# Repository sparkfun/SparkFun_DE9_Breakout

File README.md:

SparkFun DE9 Breakouts (Male and Female)
========================================
<table class="table table-hover table-striped table-bordered">
  <tr align="center">
   <td></td> 
   <td></td>
  </tr>
  <tr align="center">
    <td><a href="https://www.sparkfun.com/sparkfun-de9-breakout-male.html">SparkFun DE9 Breakout - Male <br />(BOB-29195)</a></td>
    <td><a href="https://www.sparkfun.com/sparkfun-de9-breakout-female.html">SparkFun DE9 Breakout - Female <br />(BOB-29196)</a></td>
  </tr>
</table>

The SparkFun DE9 Breakout - Male and DE9 Breakout - Female are simple breakout boards for a DE9 (commonly referred to as DB9) type connectors. These breakouts route all 9 pins from the connector, along with a pair of ground pins, to a 0.1"-spaced plated through-hole header. The boards also have two mounting holes that fit a 4-40 screw.

Repository Contents
-------------------
* **/Hardware** - Eagle design files (.brd, .sch)

Product Versions
----------------
* [BOB-29195](https://www.sparkfun.com/sparkfun-de9-breakout-male.html) - SparkFun DE9 Breakout - Male Initial Release
* [BOB-29196](https://www.sparkfun.com/sparkfun-de9-breakout-female.html) - SparkFun DE9 Breakout - Female Initial Release

License Information
-------------------

This product is _**open source**_! 

Please review the LICENSE.md file for license information. 

If you have any questions or concerns on licensing, please contact technical support on our [SparkFun forums](https://forum.sparkfun.com/viewforum.php?f=152).

Distributed as-is; no warranty is given.

- Your friends at SparkFun.

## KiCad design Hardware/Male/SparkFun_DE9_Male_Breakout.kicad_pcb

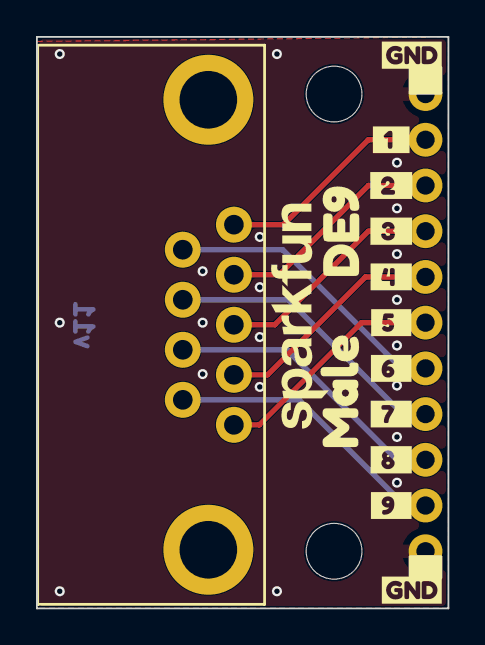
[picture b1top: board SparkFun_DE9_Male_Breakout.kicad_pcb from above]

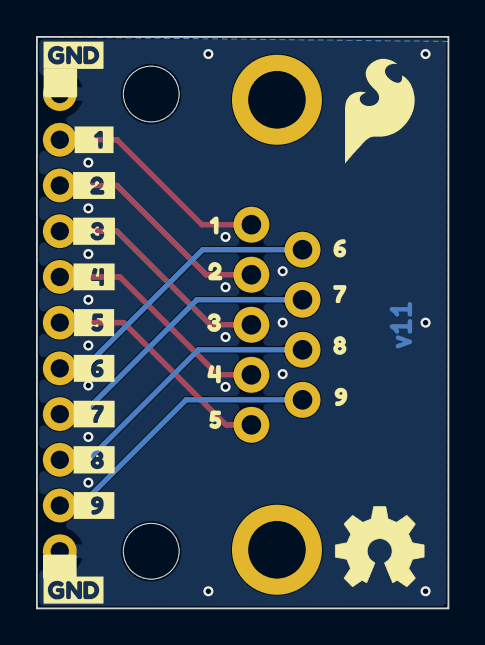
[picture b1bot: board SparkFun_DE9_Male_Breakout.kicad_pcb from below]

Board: 2 copper layers, 22.9 x 31.8 mm, 41 parts (22 on the bottom side), 10 nets.

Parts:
G3: OSHW_Logo; Creative_Commons_License
J1, J4: Conn_01x01; 1x01
J2: Conn_01x09; 1x09
J3: DE9 Header; DE9_Header_Horizontal_PTH
Ref**: Val**; OSHW_Logo_5mm
ST1, ST2: Stand_off; Standoff
kibuzzard-67D496B8: G***; kibuzzard-67D496B8
kibuzzard-67D496C7: G***; kibuzzard-67D496C7
kibuzzard-67D496CD: G***; kibuzzard-67D496CD
kibuzzard-67D496D5: G***; kibuzzard-67D496D5
kibuzzard-67D496DD: G***; kibuzzard-67D496DD
kibuzzard-67D496E4: G***; kibuzzard-67D496E4
kibuzzard-67D496EA: G***; kibuzzard-67D496EA
kibuzzard-67D496F6: G***; kibuzzard-67D496F6
kibuzzard-67D49687: G***; kibuzzard-67D49687
kibuzzard-67D49838: G***; kibuzzard-67D49838
kibuzzard-67DB37C8: G***; kibuzzard-67DB37C8
kibuzzard-67DDA3A2: G***; kibuzzard-67DDA3A2
kibuzzard-67DDA3AA: G***; kibuzzard-67DDA3AA
kibuzzard-67DDA3B0: G***; kibuzzard-67DDA3B0
kibuzzard-67DDA3B8: G***; kibuzzard-67DDA3B8
kibuzzard-67DDA3D5: G***; kibuzzard-67DDA3D5
kibuzzard-67DDA3E0: G***; kibuzzard-67DDA3E0
kibuzzard-67DDA391: G***; kibuzzard-67DDA391
kibuzzard-67DDA399: G***; kibuzzard-67DDA399
kibuzzard-67DDBC91, kibuzzard-67DDBC91#2, kibuzzard-67DDBC91#3, kibuzzard-67DDBC91#4: G***; kibuzzard-67DDBC91
kibuzzard-67DDBDB0: G***; kibuzzard-67DDBDB0
kibuzzard-67DDBDCA: G***; kibuzzard-67DDBDCA
kibuzzard-67DDBDCE: G***; kibuzzard-67DDBDCE
kibuzzard-67DDBDD2: G***; kibuzzard-67DDBDD2
kibuzzard-67DDBDD7: G***; kibuzzard-67DDBDD7
kibuzzard-67DDBDDC: G***; kibuzzard-67DDBDDC
kibuzzard-67DDBDF0: G***; kibuzzard-67DDBDF0
kibuzzard-67DDBDF6: G***; kibuzzard-67DDBDF6
kibuzzard-67DDBDFC: G***; kibuzzard-67DDBDFC
kibuzzard-67F7FDBF: G***; kibuzzard-67F7FDBF

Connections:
GND: J1.1 (Pin_1_1), J4.1 (Pin_1_1)
unnamed: J2.1, J3.1
unnamed: J2.2, J3.2
unnamed: J2.3, J3.3
unnamed: J2.4, J3.4
unnamed: J2.5, J3.5
unnamed: J2.6, J3.6
unnamed: J2.7, J3.7
unnamed: J2.8, J3.8
unnamed: J2.9, J3.9

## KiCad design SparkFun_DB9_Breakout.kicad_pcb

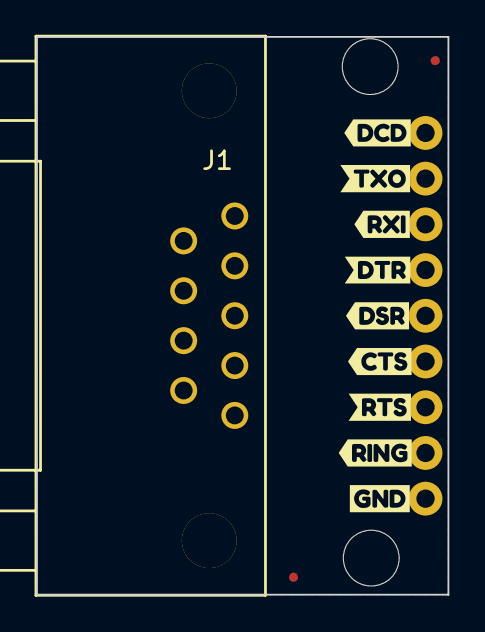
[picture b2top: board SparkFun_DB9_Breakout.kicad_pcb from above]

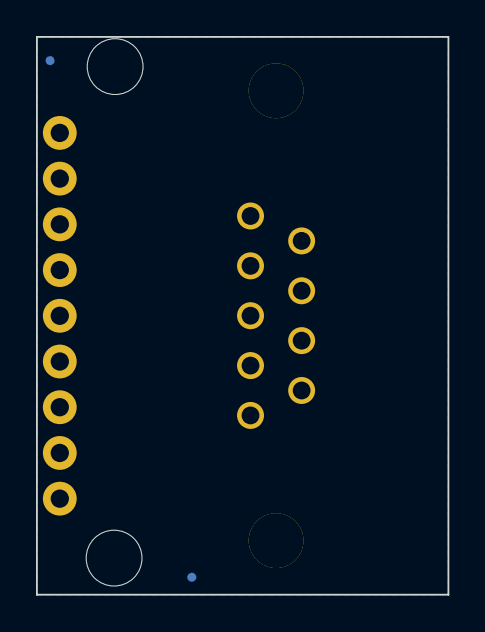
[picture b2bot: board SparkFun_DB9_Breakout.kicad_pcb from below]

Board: 4 copper layers, 22.9 x 31.0 mm, 18 parts (3 on the bottom side), 9 nets, no tracks yet.

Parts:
FID1, FID2, FID3, FID4: Fiducial_0.5mm; Fiducial_0.5mm_Mask1mm
G3: OSHW_Logo; Creative_Commons_License
J1: DB9-Female; DB9
J2: Conn_01x09; 1x09
ST1, ST2: Stand_off; Standoff
kibuzzard-67D1DAAA: G***; kibuzzard-67D1DAAA
kibuzzard-67D1DAD0: G***; kibuzzard-67D1DAD0
kibuzzard-67D1DAE5: G***; kibuzzard-67D1DAE5
kibuzzard-67D1DAFD: G***; kibuzzard-67D1DAFD
kibuzzard-67D1DB0D: G***; kibuzzard-67D1DB0D
kibuzzard-67D1DB21: G***; kibuzzard-67D1DB21
kibuzzard-67D1DB33: G***; kibuzzard-67D1DB33
kibuzzard-67D1DB48: G***; kibuzzard-67D1DB48
kibuzzard-67D1DB73: G***; kibuzzard-67D1DB73

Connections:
/CTS: J1.7 (CTS), J2.6
/DCD: J1.1 (DCD), J2.1
/DSR: J1.6 (DSR), J2.5
/DTR: J1.4 (DTR), J2.4
/RI: J1.9 (RI), J2.8
/RTS: J1.8 (RTS), J2.7
/RXD: J1.3 (RXD), J2.3
/TXD: J1.2 (TXD), J2.2
GND: J1.5 (GND), J2.9

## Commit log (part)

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2025-03-10 Initial commit with DE9 (DB9) Male/Female Footprints/Symbols
2025-03-10 Renames DE9 footprint/symbol
2025-03-12 Fixes all symbols and footprint names
2025-03-12 Adds some nets, basic outline
2025-03-12 Increases the size of the PCB
2025-03-20 Separates male/female design
2025-03-20 Adds a male footprint for the DB9 and updates the affected board
2025-03-21 Adds gitignore, Fixes Female DB9 Connector, Adds more silk, Adds GND pins
2025-03-21 Aligns symbol text
2025-03-21 Removes some files that are ignored
2025-03-21 Adds some underbars to numbers, adds silk to bottom side on male DB9
2025-03-26 Updates to the female DB9 footprint
2025-04-01 Updates the DB9 Footprint
2025-04-02 Readjusts the design to have better symmetry and layout
2025-04-02 Updates DE9 symbol
2025-04-03 Aligns GND silk
2025-04-03 Removes all reference to "DB9" to it's correct name "DE9"
2025-04-03 Updates symbol, footprint, and design with the new renamed parts
2025-04-03 Updates DE9 layout by placing components more consistently on grid
2025-04-03 Moves standoff just a bit
2025-04-03 Fixes measure at standoff
2025-04-03 Updates pinout table in the schematic
2025-04-03 Fixes common pinouts tables in schematics
2025-04-10 Updates teh footprints of the DE9 connector to match the symbol
2025-04-10 Updates male breakout with new footprint
2025-04-25 Removes the local symbols/footprints, moves designs to Hardware folder
2025-04-25 Updates DE9 footprints on both designs
2025-07-14 Update README.md
    Updating readme from template.
2025-10-21 Fixes silk and pinout on DE9 connector
2025-12-04 Fix table
    Change RTS to DSR on pin 6

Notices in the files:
parts and their libraries:
Released under the Creative Commons Attribution Share-Alike 4.0 License
https://creativecommons.org/licenses/by-sa/4.0
